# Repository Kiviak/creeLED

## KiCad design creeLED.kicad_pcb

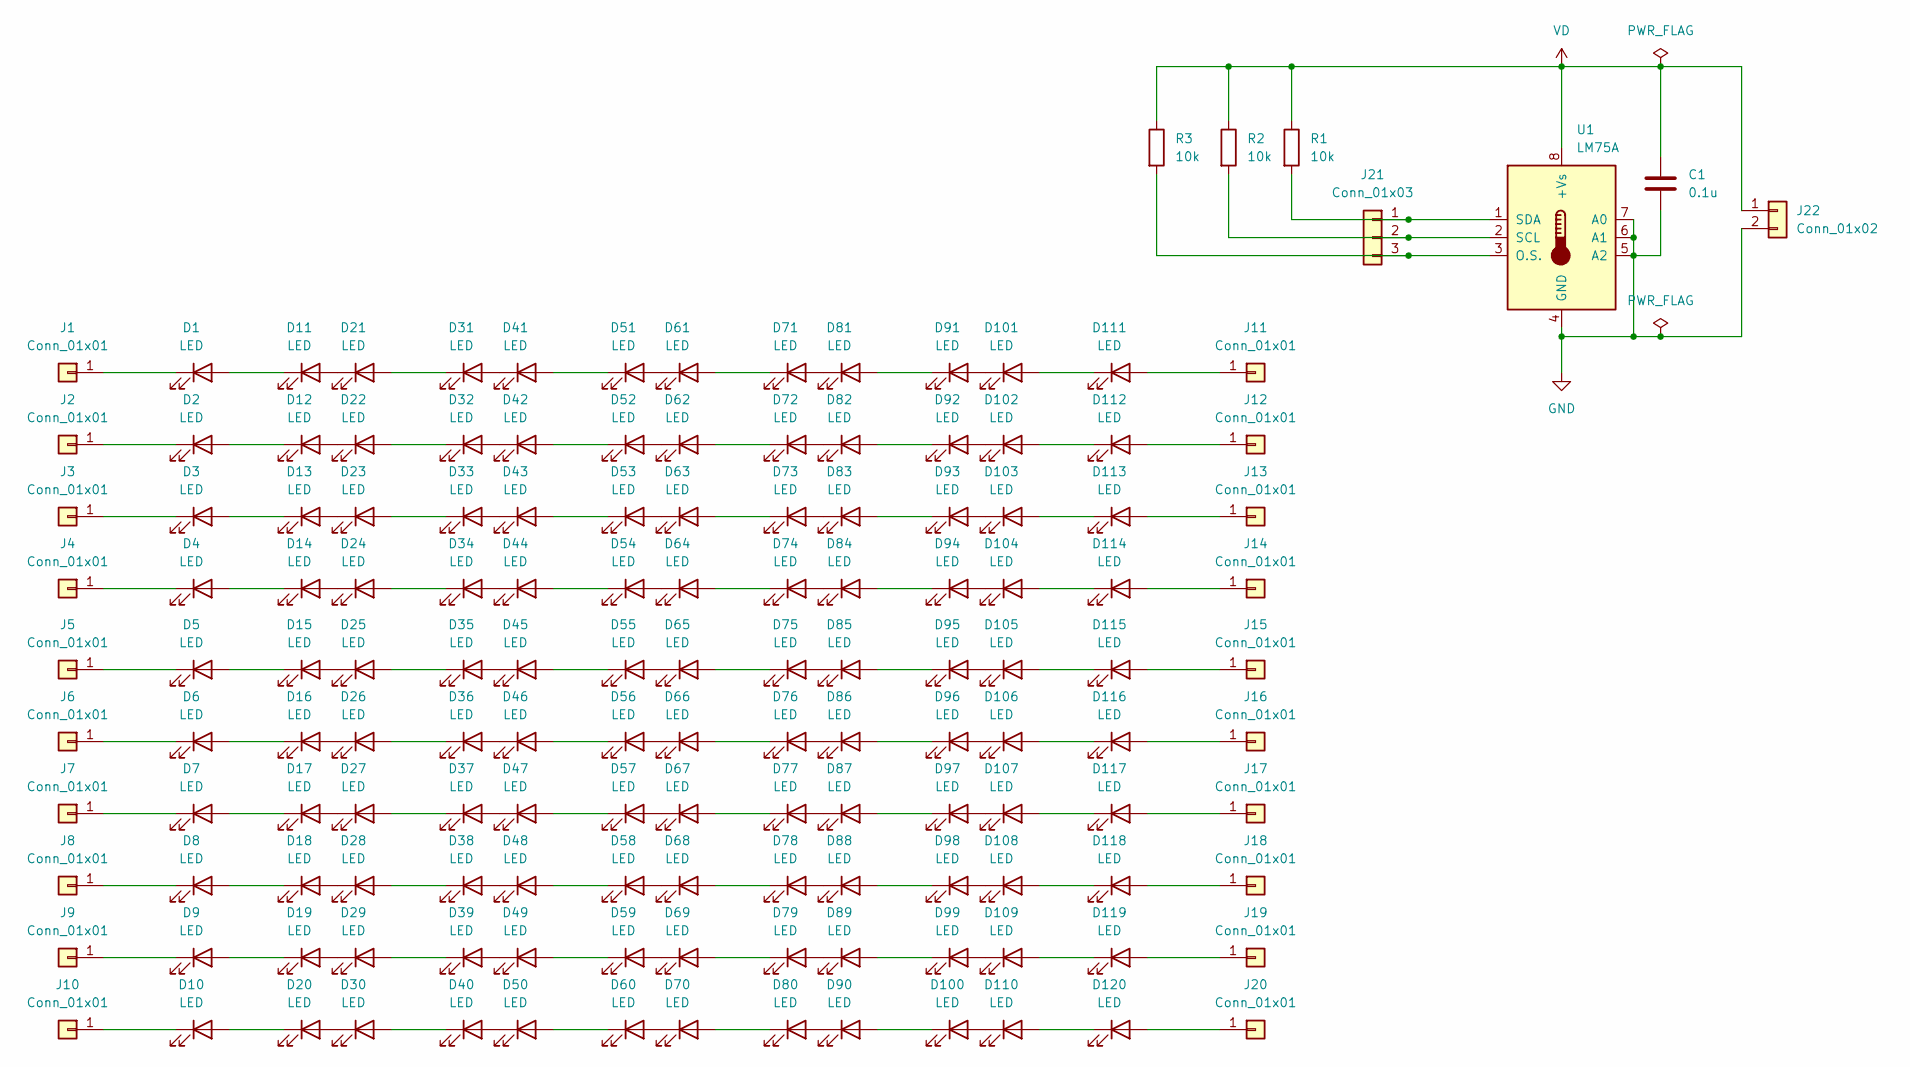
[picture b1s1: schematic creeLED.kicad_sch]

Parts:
C1: 0.1u; C_0603_1608Metric_Pad1.08x0.95mm_HandSolder
D1, D2, D3, D4, D5, D6, D7, D8, D9, D10, D11, D12, D13, D14, D15, D16, D17, D18, D19, D20, D21, D22, D23, D24, D25, D26, D27, D28, D29, D30, D31, D32, D33, D34, D35, D36, D37, D38, D39, D40, D41, D42, D43, D44, D45, D46, D47, D48, D49, D50, D51, D52, D53, D54, D55, D56, D57, D58, D59, D60, D61, D62, D63, D64, D65, D66, D67, D68, D69, D70, D71, D72, D73, D74, D75, D76, D77, D78, D79, D80, D81, D82, D83, D84, D85, D86, D87, D88, D89, D90, D91, D92, D93, D94, D95, D96, D97, D98, D99, D100, D101, D102, D103, D104, D105, D106, D107, D108, D109, D110, D111, D112, D113, D114, D115, D116, D117, D118, D119, D120: LED; Cree_J-Series-2835-LED
J1, J2, J3, J4, J5, J6, J7, J8, J9, J10, J11, J12, J13, J14, J15, J16, J17, J18, J19, J20: Conn_01x01; led_power_pin1
J21: Conn_01x03; I2S
J22: Conn_01x02; power_2pin
R1, R2, R3: 10k; R_0603_1608Metric_Pad0.98x0.95mm_HandSolder
U1: LM75A; HSOP-8-1EP_3.9x4.9mm_P1.27mm_EP2.41x3.1mm

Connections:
GND: C1.2, J22.2, U1.4 (GND), U1.5 (A2), U1.6 (A1), U1.7 (A0)
unnamed: D1.1 (K), J1.1
unnamed: D1.2 (A), D11.1 (K)
unnamed: D2.1 (K), J2.1
unnamed: D3.1 (K), J3.1
unnamed: D4.1 (K), J4.1
unnamed: D5.1 (K), J5.1
unnamed: D6.1 (K), J6.1
unnamed: D7.1 (K), J7.1
unnamed: D8.1 (K), J8.1
unnamed: D9.1 (K), J9.1
unnamed: D10.1 (K), J10.1
unnamed: D10.2 (A), D20.1 (K)
unnamed: D11.2 (A), D21.1 (K)
unnamed: D2.2 (A), D12.1 (K)
unnamed: D12.2 (A), D22.1 (K)
unnamed: D3.2 (A), D13.1 (K)
unnamed: D13.2 (A), D23.1 (K)
unnamed: D4.2 (A), D14.1 (K)
unnamed: D14.2 (A), D24.1 (K)
unnamed: D5.2 (A), D15.1 (K)
unnamed: D15.2 (A), D25.1 (K)
unnamed: D6.2 (A), D16.1 (K)
unnamed: D16.2 (A), D26.1 (K)
unnamed: D7.2 (A), D17.1 (K)
unnamed: D17.2 (A), D27.1 (K)
unnamed: D8.2 (A), D18.1 (K)
unnamed: D18.2 (A), D28.1 (K)
unnamed: D9.2 (A), D19.1 (K)
unnamed: D19.2 (A), D29.1 (K)
unnamed: D20.2 (A), D30.1 (K)
unnamed: D21.2 (A), D31.1 (K)
unnamed: D22.2 (A), D32.1 (K)
unnamed: D23.2 (A), D33.1 (K)
unnamed: D24.2 (A), D34.1 (K)
unnamed: D25.2 (A), D35.1 (K)
unnamed: D26.2 (A), D36.1 (K)
unnamed: D27.2 (A), D37.1 (K)
unnamed: D28.2 (A), D38.1 (K)
unnamed: D29.2 (A), D39.1 (K)
unnamed: D30.2 (A), D40.1 (K)
unnamed: D31.2 (A), D41.1 (K)
unnamed: D32.2 (A), D42.1 (K)
unnamed: D33.2 (A), D43.1 (K)
unnamed: D34.2 (A), D44.1 (K)
unnamed: D35.2 (A), D45.1 (K)
unnamed: D36.2 (A), D46.1 (K)
unnamed: D37.2 (A), D47.1 (K)
unnamed: D38.2 (A), D48.1 (K)
unnamed: D39.2 (A), D49.1 (K)
unnamed: D40.2 (A), D50.1 (K)
unnamed: D41.2 (A), D51.1 (K)
unnamed: D42.2 (A), D52.1 (K)
unnamed: D43.2 (A), D53.1 (K)
unnamed: D44.2 (A), D54.1 (K)
unnamed: D45.2 (A), D55.1 (K)
unnamed: D46.2 (A), D56.1 (K)
unnamed: D47.2 (A), D57.1 (K)
unnamed: D48.2 (A), D58.1 (K)
unnamed: D49.2 (A), D59.1 (K)
unnamed: D50.2 (A), D60.1 (K)
unnamed: D51.2 (A), D61.1 (K)
unnamed: D52.2 (A), D62.1 (K)
unnamed: D53.2 (A), D63.1 (K)
unnamed: D54.2 (A), D64.1 (K)
unnamed: D55.2 (A), D65.1 (K)
unnamed: D56.2 (A), D66.1 (K)
unnamed: D57.2 (A), D67.1 (K)
unnamed: D58.2 (A), D68.1 (K)
unnamed: D59.2 (A), D69.1 (K)
unnamed: D60.2 (A), D70.1 (K)
unnamed: D61.2 (A), D71.1 (K)
unnamed: D62.2 (A), D72.1 (K)
unnamed: D63.2 (A), D73.1 (K)
unnamed: D64.2 (A), D74.1 (K)
unnamed: D65.2 (A), D75.1 (K)
unnamed: D66.2 (A), D76.1 (K)
unnamed: D67.2 (A), D77.1 (K)
unnamed: D68.2 (A), D78.1 (K)
unnamed: D69.2 (A), D79.1 (K)
unnamed: D70.2 (A), D80.1 (K)
unnamed: D71.2 (A), D81.1 (K)
unnamed: D72.2 (A), D82.1 (K)
unnamed: D73.2 (A), D83.1 (K)
unnamed: D74.2 (A), D84.1 (K)
unnamed: D75.2 (A), D85.1 (K)
unnamed: D76.2 (A), D86.1 (K)
unnamed: D77.2 (A), D87.1 (K)
unnamed: D78.2 (A), D88.1 (K)
unnamed: D79.2 (A), D89.1 (K)
unnamed: D80.2 (A), D90.1 (K)
unnamed: D81.2 (A), D91.1 (K)
unnamed: D82.2 (A), D92.1 (K)
unnamed: D83.2 (A), D93.1 (K)
unnamed: D84.2 (A), D94.1 (K)
unnamed: D85.2 (A), D95.1 (K)
unnamed: D86.2 (A), D96.1 (K)
unnamed: D87.2 (A), D97.1 (K)
unnamed: D88.2 (A), D98.1 (K)
unnamed: D89.2 (A), D99.1 (K)
unnamed: D90.2 (A), D100.1 (K)
unnamed: D100.2 (A), D110.1 (K)
unnamed: D91.2 (A), D101.1 (K)
unnamed: D101.2 (A), D111.1 (K)
unnamed: D92.2 (A), D102.1 (K)
unnamed: D102.2 (A), D112.1 (K)
unnamed: D93.2 (A), D103.1 (K)
unnamed: D103.2 (A), D113.1 (K)
unnamed: D94.2 (A), D104.1 (K)
unnamed: D104.2 (A), D114.1 (K)
unnamed: D95.2 (A), D105.1 (K)
unnamed: D105.2 (A), D115.1 (K)
unnamed: D96.2 (A), D106.1 (K)
unnamed: D106.2 (A), D116.1 (K)
unnamed: D97.2 (A), D107.1 (K)
unnamed: D107.2 (A), D117.1 (K)
unnamed: D98.2 (A), D108.1 (K)
unnamed: D108.2 (A), D118.1 (K)
unnamed: D99.2 (A), D109.1 (K)
unnamed: D109.2 (A), D119.1 (K)
unnamed: D110.2 (A), D120.1 (K)
unnamed: D111.2 (A), J11.1
unnamed: D112.2 (A), J12.1
unnamed: D113.2 (A), J13.1
unnamed: D114.2 (A), J14.1
unnamed: D115.2 (A), J15.1
unnamed: D116.2 (A), J16.1
unnamed: D117.2 (A), J17.1
unnamed: D118.2 (A), J18.1
unnamed: D119.2 (A), J19.1
unnamed: D120.2 (A), J20.1
unnamed: J21.1, R1.2, U1.1 (SDA)
unnamed: J21.2, R2.2, U1.2 (SCL)
unnamed: J21.3, R3.2, U1.3 (O.S.)
VD: C1.1, J22.1, R1.1, R2.1, R3.1, U1.8 (+Vs)

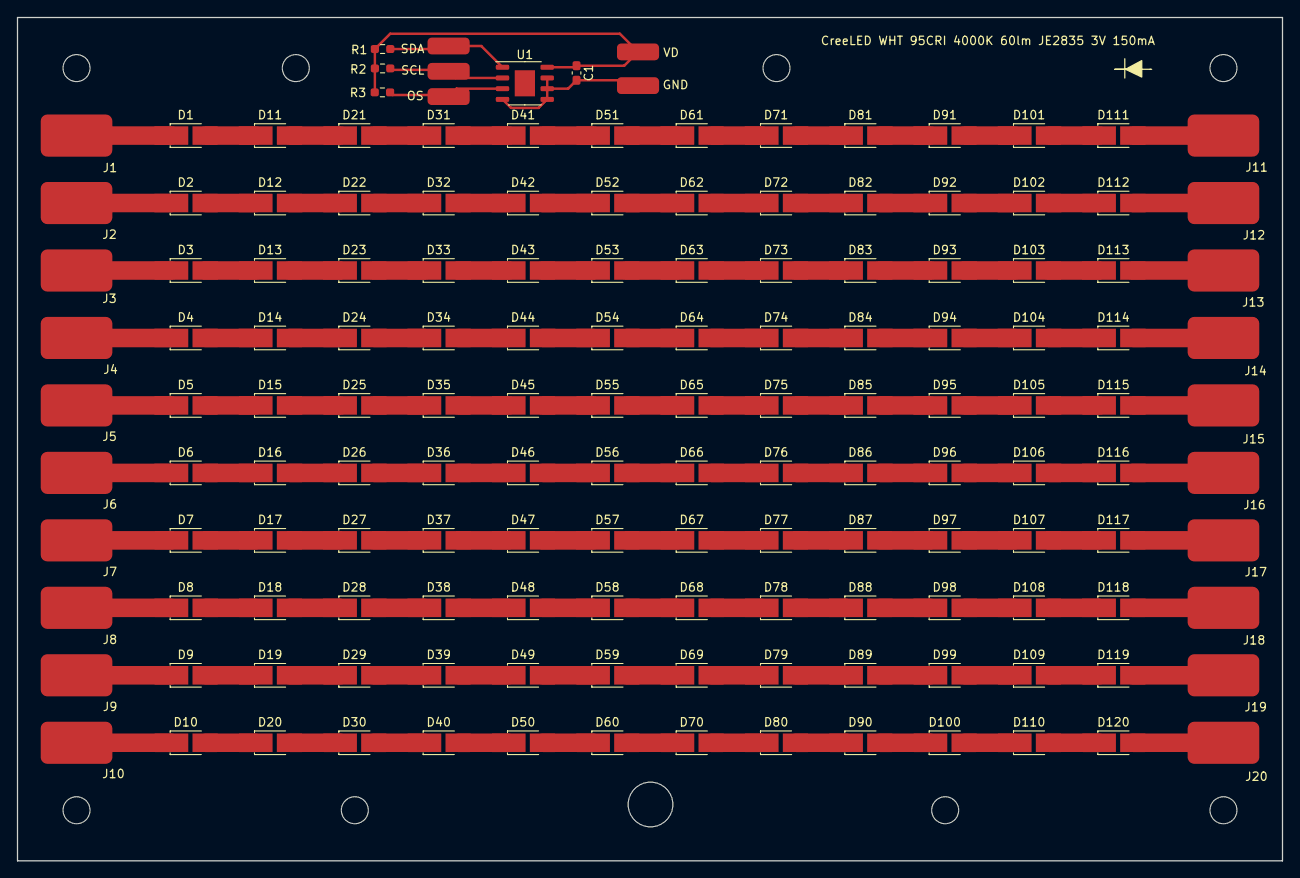
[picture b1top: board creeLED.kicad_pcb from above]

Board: 2 copper layers, 150.0 x 100.0 mm, 147 parts (0 on the bottom side), 135 nets.

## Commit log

2022-09-18 v1.0
2022-09-26 v1.1
